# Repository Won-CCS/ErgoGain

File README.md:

# ErgoGain

## Hardware
- See `kicad/` (schematics, PCB, BOM, gerbers)

## Firmware (QMK)
This repo uses a submodule for firmware:
- Repo: https://github.com/Won-CCS/qmk_firmware
- Locked commit: `77456cc`

### Build
```bash
git clone https://github.com/Won-CCS/ErgoGain.git
cd ErgoGain
git submodule update --init --recursive

cd firmware
qmk compile -kb ergogain -km default

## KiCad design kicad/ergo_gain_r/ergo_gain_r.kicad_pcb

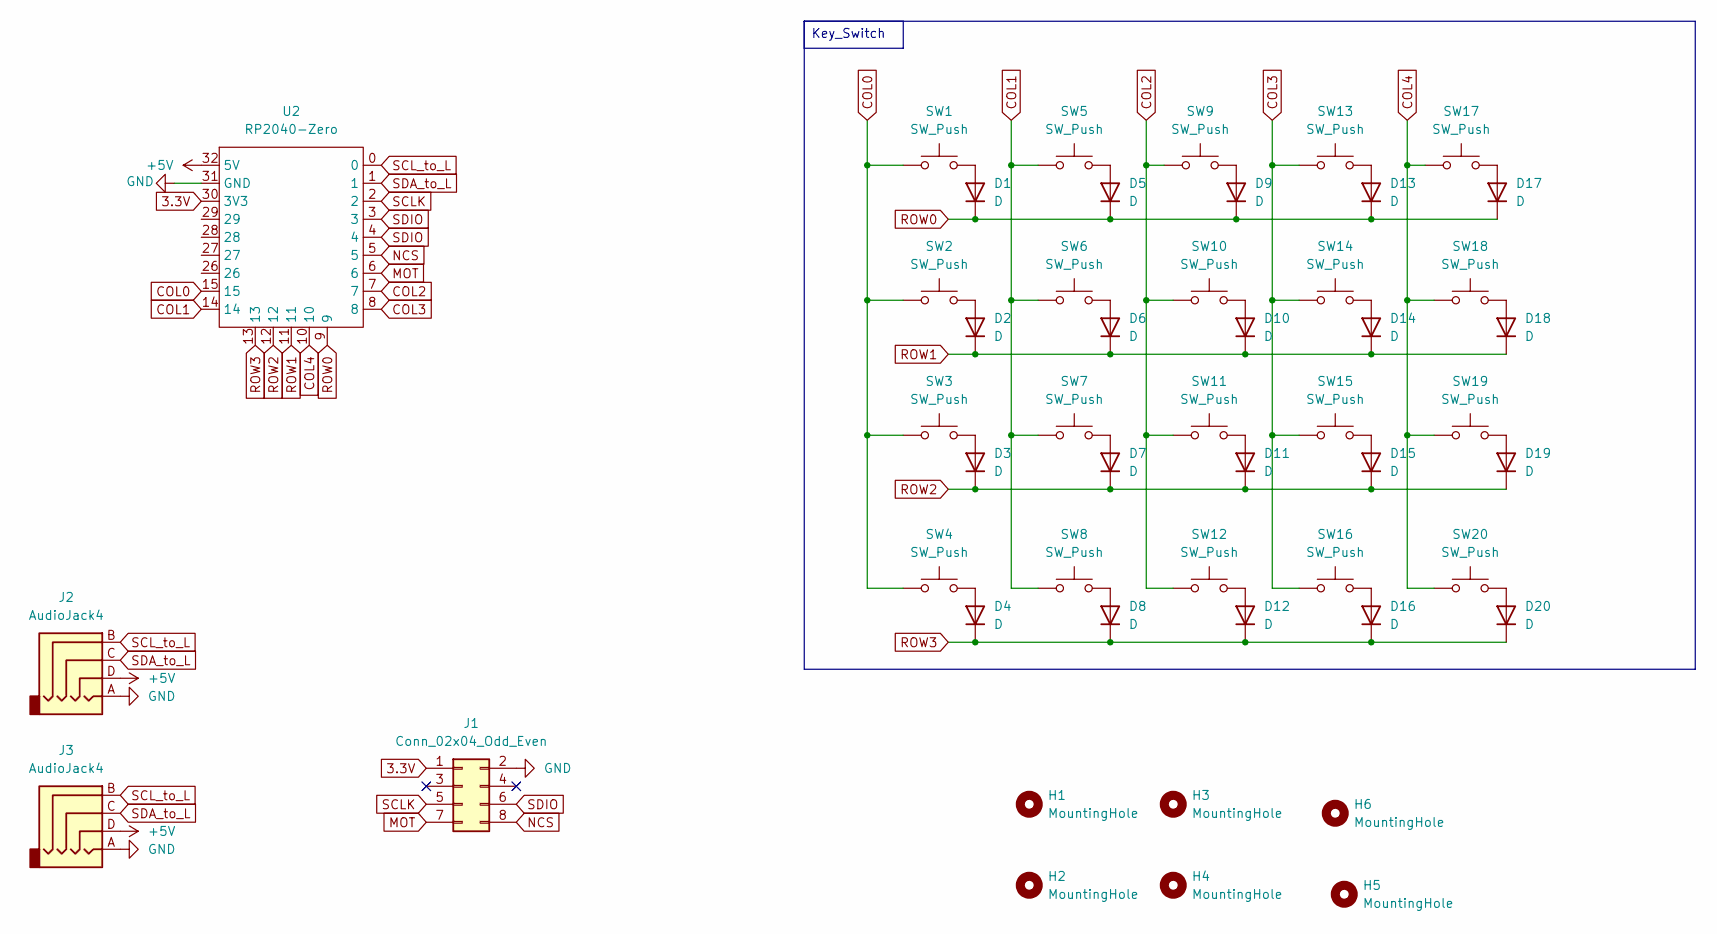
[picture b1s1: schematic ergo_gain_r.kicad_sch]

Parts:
D1, D2, D3, D4, D5, D6, D7, D8, D9, D10, D11, D12, D13, D14, D15, D16, D17, D18, D19, D20: D; 1N4148W; LCSC C81598
H1, H2, H3, H4, H5, H6: MountingHole; MountingHole_4.3mm_M4
J1: Conn_02x04_Odd_Even; PinSocket_2x04_P2.54mm_Vertical
J2, J3: AudioJack4; TRRS_PJ-320A
SW1, SW2, SW3, SW4, SW5, SW6, SW7, SW8, SW9, SW10, SW11, SW12, SW13, SW14, SW15, SW16, SW17, SW18, SW19, SW20: SW_Push; MX_socket
U2: RP2040-Zero; RP2040-Zero-THT

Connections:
3.3V: J1.1, U2.30 (3V3)
+5V: J2.D, J3.D, U2.32 (5V)
COL0: SW1.1, SW2.1, SW3.1, SW4.1, U2.15
COL1: SW5.1, SW6.1, SW7.1, SW8.1, U2.14
COL2: SW9.1, SW10.1, SW11.1, SW12.1, U2.7
COL3: SW13.1, SW14.1, SW15.1, SW16.1, U2.8
COL4: SW17.1, SW18.1, SW19.1, SW20.1, U2.10
GND: J1.2, J2.A, J3.A, U2.31 (GND)
MOT: J1.7, U2.6
NCS: J1.8, U2.5
unnamed: D1.2 (A), SW1.2
unnamed: D2.2 (A), SW2.2
unnamed: D3.2 (A), SW3.2
unnamed: D4.2 (A), SW4.2
unnamed: D5.2 (A), SW5.2
unnamed: D6.2 (A), SW6.2
unnamed: D7.2 (A), SW7.2
unnamed: D8.2 (A), SW8.2
unnamed: D9.2 (A), SW9.2
unnamed: D10.2 (A), SW10.2
unnamed: D11.2 (A), SW11.2
unnamed: D12.2 (A), SW12.2
unnamed: D13.2 (A), SW13.2
unnamed: D14.2 (A), SW14.2
unnamed: D15.2 (A), SW15.2
unnamed: D16.2 (A), SW16.2
unnamed: D17.2 (A), SW17.2
unnamed: D18.2 (A), SW18.2
unnamed: D19.2 (A), SW19.2
unnamed: D20.2 (A), SW20.2
ROW0: D1.1 (K), D5.1 (K), D9.1 (K), D13.1 (K), D17.1 (K), U2.9
ROW1: D2.1 (K), D6.1 (K), D10.1 (K), D14.1 (K), D18.1 (K), U2.11
ROW2: D3.1 (K), D7.1 (K), D11.1 (K), D15.1 (K), D19.1 (K), U2.12
ROW3: D4.1 (K), D8.1 (K), D12.1 (K), D16.1 (K), D20.1 (K), U2.13
SCLK: J1.5, U2.2
SCL_to_L: J2.B, J3.B, U2.0
SDA_to_L: J2.C, J3.C, U2.1
SDIO: J1.6, U2.3, U2.4

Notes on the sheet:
Key_Switch

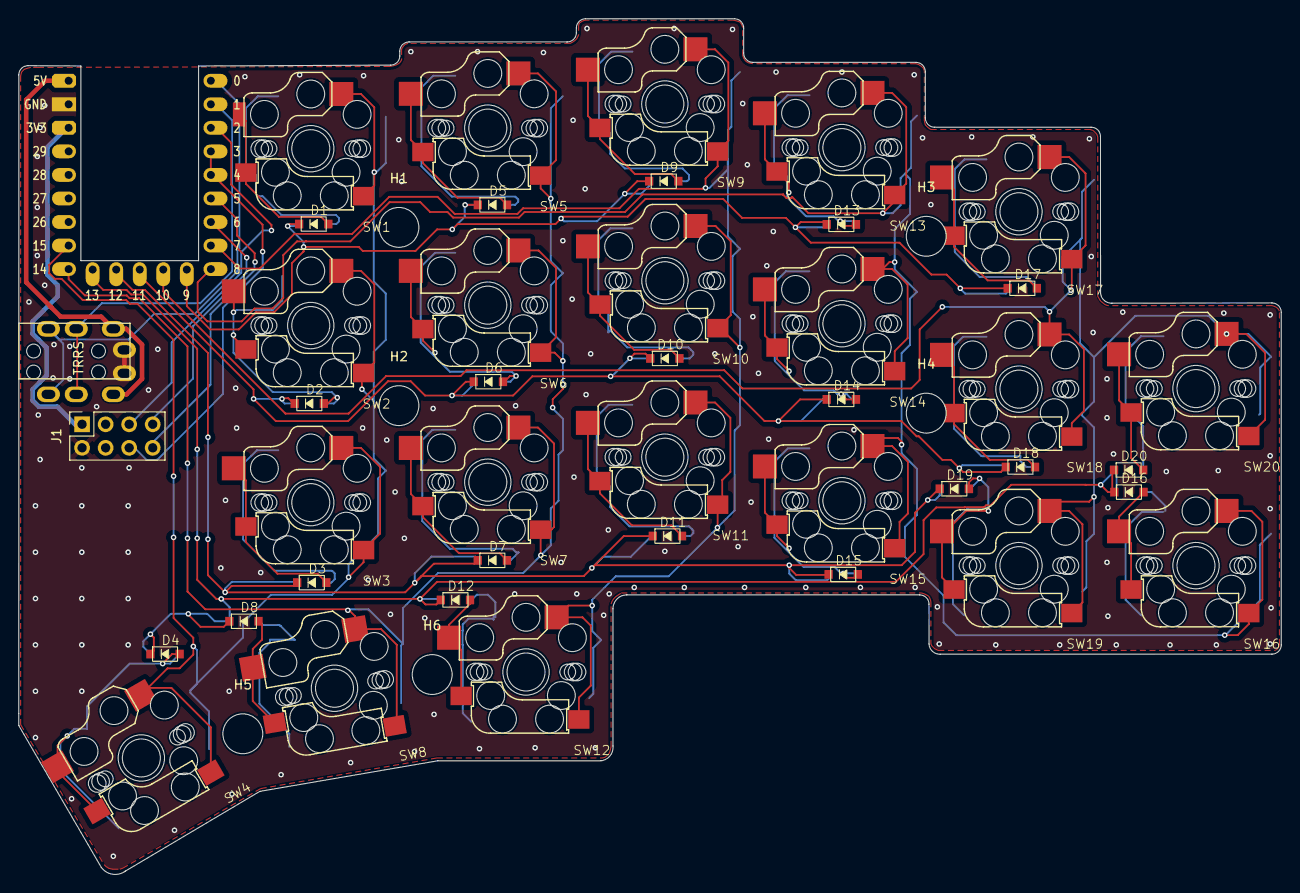
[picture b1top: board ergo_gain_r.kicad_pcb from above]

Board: 2 copper layers, 136.2 x 92.3 mm, 50 parts (1 on the bottom side), 38 nets.

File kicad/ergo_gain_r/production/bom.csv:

Designator,Footprint,Quantity,Value,LCSC Part #
"D1, D10, D11, D12, D13, D14, D15, D16, D17, D18, D19, D2, D20, D3, D4, D5, D6, D7, D8, D9",1N4148W,20,D,C81598
"H1, H2, H3, H4, H5",MountingHole_4.3mm_M4,5,MountingHole,
J1,PinSocket_2x04_P2.54mm_Vertical,1,Conn_02x04_Odd_Even,
"J2, J3",TRRS_PJ-320A,2,AudioJack4,
"SW1, SW10, SW11, SW12, SW13, SW14, SW15, SW16, SW17, SW18, SW19, SW2, SW20, SW3, SW4, SW5, SW6, SW7, SW8, SW9",MX_socket,20,SW_Push,
U2,RP2040-Zero-THT,1,RP2040-Zero,

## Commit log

2025-10-04 first
2025-10-04 Add firmware submodule (QMK fork)
2025-10-04 Bump firmware submodule to <shortsha> (PMW3610 + Ergogain)
2025-10-04 add README
